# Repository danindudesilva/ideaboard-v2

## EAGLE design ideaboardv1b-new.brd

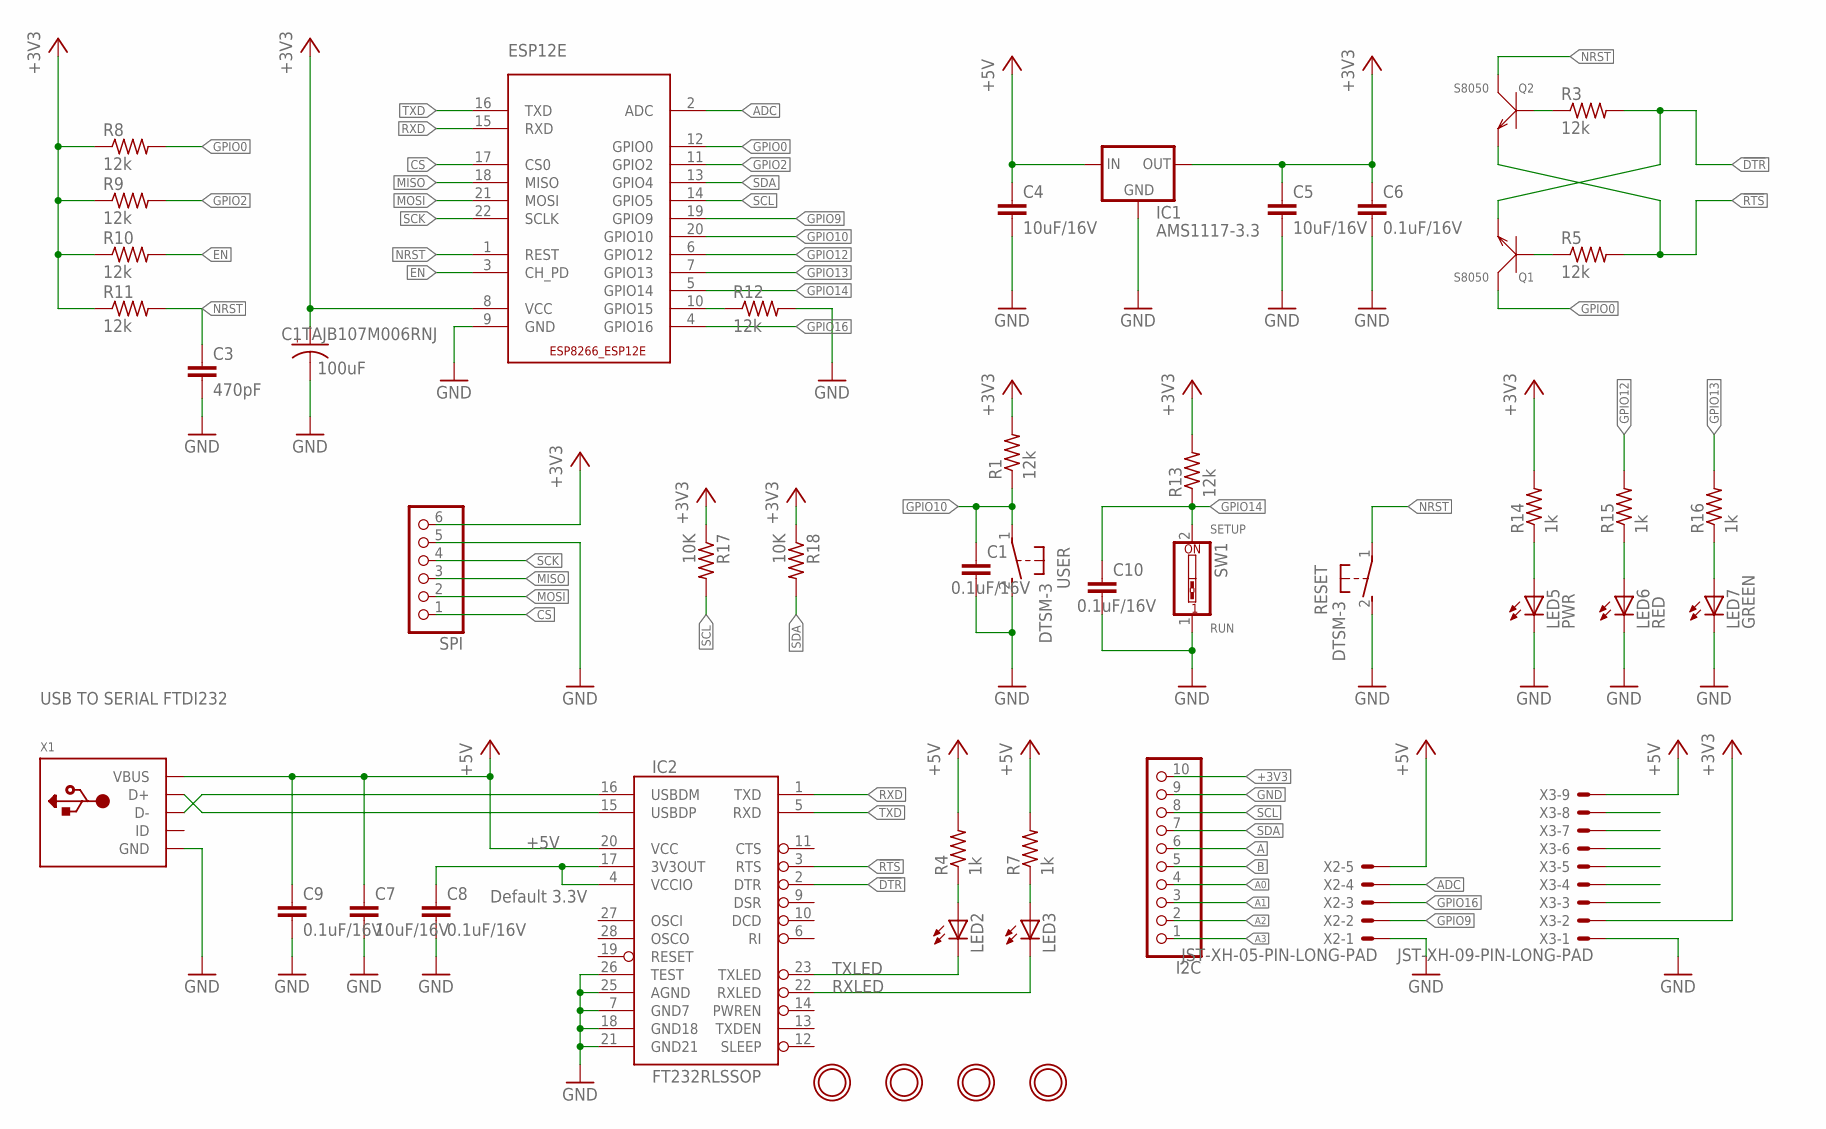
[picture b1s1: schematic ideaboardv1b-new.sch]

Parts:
C1, C6, C8, C9, C10: 0.1uF/16V; C0805K
C1TAJB107M006RNJ: 100uF; A/3216-18R
C3: 470pF; C0805K
C4, C5, C7: 10uF/16V; C0805K
ESP12E: ESP8266-12EESP8266-ESP12E; ESP8266-ESP12E
I2C: PINHD-1X10; 1X10
IC1: AMS1117-3.3; SOT223
IC2: FT232RLSSOP; SSOP28DB
LED2, LED3: LEDCHIP-LED0805; CHIP-LED0805
LED5: PWR; CHIP-LED0805
LED6: RED; CHIP-LED0805
LED7: GREEN; CHIP-LED0805
Q1, Q2: S8050; SOT-23
R1, R3, R5, R8, R9, R10, R11, R12, R13: 12k; M0805
R4, R7, R14, R15, R16: 1k; M0805
R17, R18: 10K; M0805
RESET: DTSM-3
SPI: PINHD-1X6; 1X06
SW1: SW_DIP-1; EDG-01
U$1, U$2, U$3, U$4: MOUNTINGHOLE2.0; MOUNTINGHOLE_2.0_PLATED
USER: DTSM-3
X1: USB_MICRO_20329_V2; 4UCONN_20329_V2
X2: JST-XH-05-PIN-LONG-PAD; JST-XH-05-PACKAGE-LONG-PAD
X3: JST-XH-09-PIN-LONG-PAD; JST-XH-09-PACKAGE-LONG-PAD

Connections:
!DTR: IC2.2 (DTR), Q1.2 (E), R3.2
!RTS: IC2.3 (RTS), Q2.2 (E), R5.2
+3V3: C1TAJB107M006RNJ.+, C5.1, C6.1, ESP12E.8 (VCC), I2C.10, IC1.2 (OUT), R1.2, R8.1, R9.1, R10.1, R11.1, R13.2, R14.2, R17.1, R18.1, SPI.6, X3.2
+5V: C4.1, C7.1, C9.1, IC1.3 (IN), IC2.20 (VCC), R4.2, R7.2, X1.VBUS, X2.5, X3.9
A: I2C.6, X3.3
A0: I2C.4, X3.5
A1: I2C.3, X3.6
A2: I2C.2, X3.7
A3: I2C.1, X3.8
ADC: ESP12E.2 (ADC), X2.4
B: I2C.5, X3.4
CS: ESP12E.17 (CS0), SPI.1
EN: ESP12E.3 (CH_PD), R10.2
GND: C1.2, C1TAJB107M006RNJ.-, C3.2, C4.2, C5.2, C6.2, C7.2, C8.2, C9.2, C10.2, ESP12E.9 (GND), I2C.9, IC1.1 (GND), IC2.7 (GND7), IC2.18 (GND18), IC2.21 (GND21), IC2.25 (AGND), IC2.26 (TEST), LED5.C, LED6.C, LED7.C, R12.2, RESET.2, SPI.5, SW1.1, USER.2, X1.BASE@1 (GND), X1.BASE@2 (GND), X1.GND, X1.SPRT@1 (GND), X1.SPRT@2 (GND), X1.SPRT@3 (GND), X1.SPRT@4 (GND), X2.1, X3.1
GPIO0: ESP12E.12 (GPIO0), Q1.3 (C), R8.2
GPIO2: ESP12E.11 (GPIO2), R9.2
GPIO9: ESP12E.19 (GPIO9), X2.2
GPIO10: C1.1, ESP12E.20 (GPIO10), R1.1, USER.1
GPIO12: ESP12E.6 (GPIO12), R15.2
GPIO13: ESP12E.7 (GPIO13), R16.2
GPIO14: C10.1, ESP12E.5 (GPIO14), R13.1, SW1.2
GPIO16: ESP12E.4 (GPIO16), X2.3
MISO: ESP12E.18 (MISO), SPI.3
MOSI: ESP12E.21 (MOSI), SPI.2
unnamed: Q2.1 (B), R3.1
unnamed: Q1.1 (B), R5.1
unnamed: ESP12E.10 (GPIO15), R12.1
unnamed: C8.1, IC2.4 (VCCIO), IC2.17 (3V3OUT)
unnamed: LED5.A, R14.1
unnamed: LED2.A, R4.1
unnamed: LED6.A, R15.1
unnamed: LED3.A, R7.1
unnamed: LED7.A, R16.1
NRST: C3.1, ESP12E.1 (REST), Q2.3 (C), R11.2, RESET.1
RXD: ESP12E.15 (RXD), IC2.1 (TXD)
RXLED: IC2.22 (RXLED), LED3.C
SCK: ESP12E.22 (SCLK), SPI.4
SCL: ESP12E.14 (GPIO5), I2C.8, R17.2
SDA: ESP12E.13 (GPIO4), I2C.7, R18.2
TXD: ESP12E.16 (TXD), IC2.5 (RXD)
TXLED: IC2.23 (TXLED), LED2.C
USB_D+: IC2.15 (USBDP), X1.D+
USB_D-: IC2.16 (USBDM), X1.D-

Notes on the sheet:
Default 3.3V
USB TO SERIAL FTDI232
RUN
SETUP

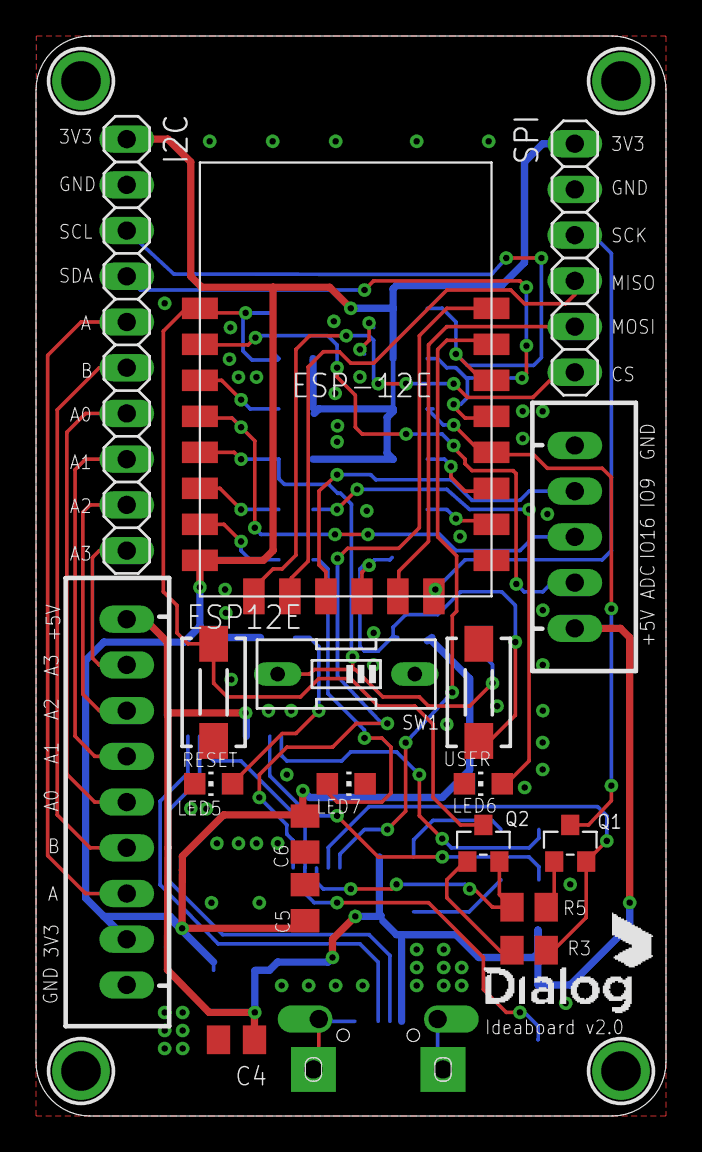
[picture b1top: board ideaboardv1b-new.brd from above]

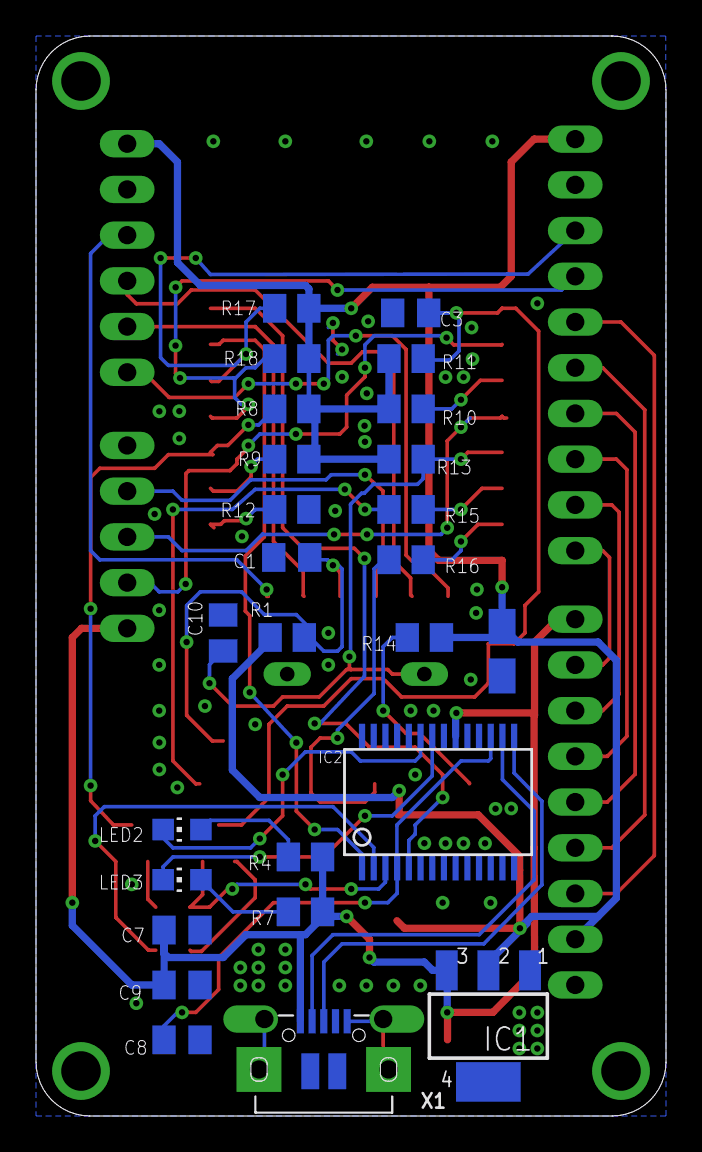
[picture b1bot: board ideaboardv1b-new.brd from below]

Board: 2 copper layers, 35.0 x 60.0 mm, 48 parts (26 on the bottom side), 43 nets.
